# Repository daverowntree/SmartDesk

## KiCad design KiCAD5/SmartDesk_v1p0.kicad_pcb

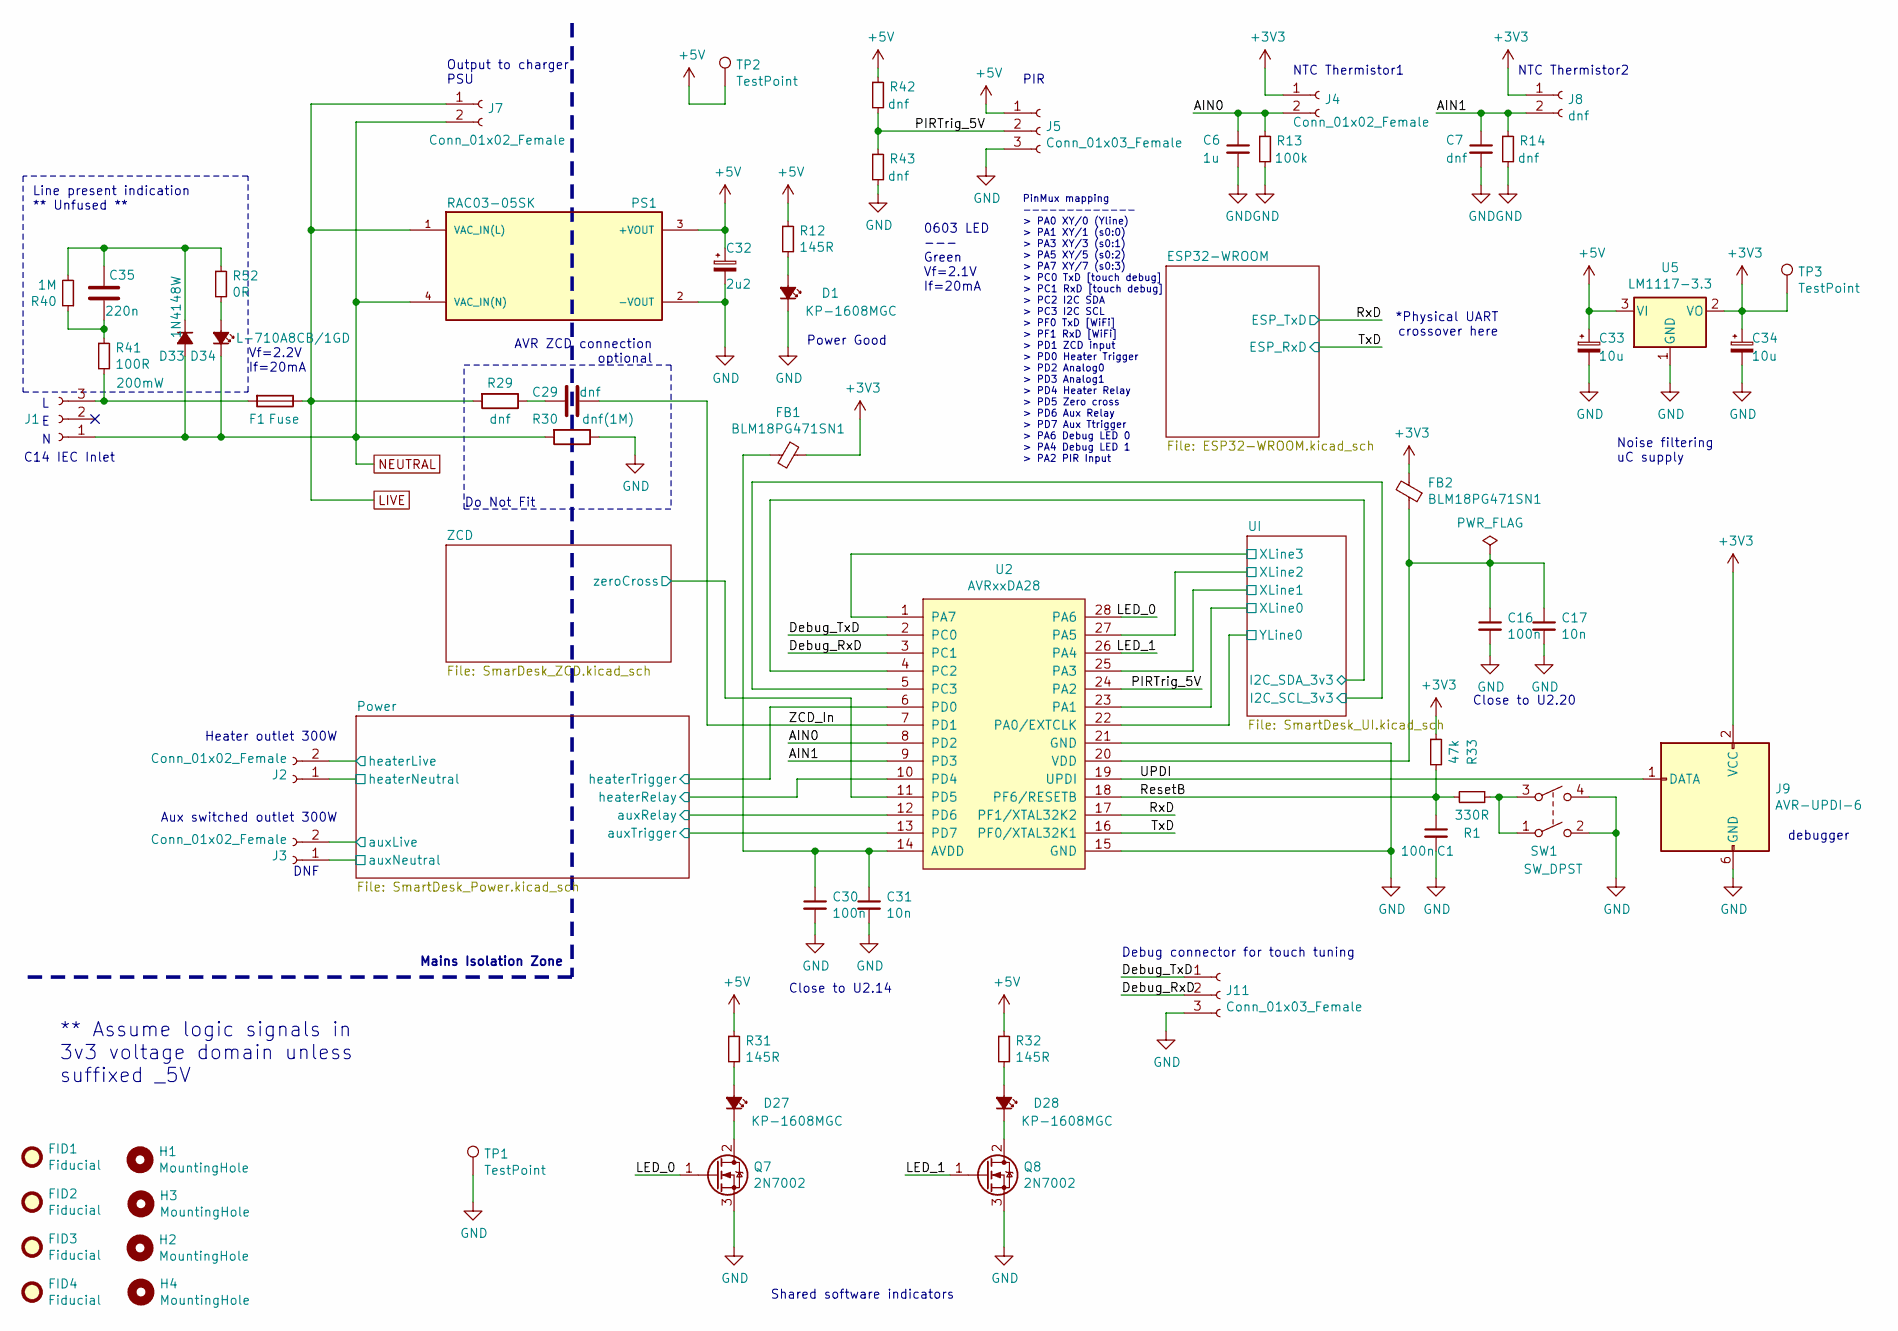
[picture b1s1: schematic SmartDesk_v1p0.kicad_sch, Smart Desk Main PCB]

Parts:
C1, C16, C30: 100n; C_0603_1608Metric
C6: 1u; C_0603_1608Metric
C7: dnf; C_0603_1608Metric
C17, C31: 10n; C_0603_1608Metric
C29: dnf; C_0805_2012Metric
C32: 2u2; C_0805_2012Metric
C33, C34: 10u; C_0805_2012Metric
C35: 220n; B32922C3224
D1, D27, D28: KP-1608MGC; LED_0603_1608Metric
D33: 1N4148W; D_SOD-323
D34: L-710A8CB/1GD; L-710A8CB
F1: Fuse; Bulgin-FX0321
FB1, FB2: BLM18PG471SN1; C_0603_1608Metric
FID1, FID2, FID3, FID4: Fiducial; Fiducial_Modern_CopperTop
H1, H2, H3, H4: MountingHole; MountingHole_4.3mm_M4
J1: Conn_01x03_Female; Bulgin-PX0580-PC
J2, J3, J7: Conn_01x02_Female; TerminalBlock_Phoenix_MKDS-3-2-5.08_1x02_P5.08mm_Horizontal
J4: Conn_01x02_Female; JST_PH_B2B-PH-K_1x02_P2.00mm_Vertical
J5: Conn_01x03_Female; JST_PH_B3B-PH-K_1x03_P2.00mm_Vertical
J8: dnf; JST_PH_B2B-PH-K_1x02_P2.00mm_Vertical
J9: AVR-UPDI-6; PinHeader_2x03_P2.54mm_Vertical
J11: Conn_01x03_Female; PinHeader_1x03_P2.54mm_Vertical
PS1: RAC03-05SK; CONV_RAC03-05SK
Q7, Q8: 2N7002; SOT-23
R1: 330R; R_0603_1608Metric
R12, R31, R32: 145R; R_0603_1608Metric
R13: 100k; R_0603_1608Metric
R14, R42, R43: dnf; R_0603_1608Metric
R29: dnf; R_0805_2012Metric
R30: dnf(1M); R_0805_2012Metric
R33: 47k; R_0603_1608Metric
R40: 1M; R_0603_1608Metric
R41: 100R; R_1206_3216Metric
R52: 0R; R_0603_1608Metric
SW1: SW_DPST; 2-1437565-8
TP1: TestPoint; TestPoint_Loop_D1.80mm_Drill1.0mm_Beaded
TP2, TP3: TestPoint; TestPoint_Pad_D2.0mm
U2: AVRxxDA28; SOIC-28W_7.5x17.9mm_P1.27mm
U5: LM1117-3.3; SOT-223-lm1117

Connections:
+3V3: C34.1, FB1.1, FB2.2, J4.1, J8.1, J9.2 (VCC), R33.1, TP3.1, U5.2 (VO); also elsewhere on the board
+5V: C32.1, C33.1, J5.1, PS1.3 (+VOUT), R12.1, R31.1, R32.1, R42.1, TP2.1, U5.3 (VI); also elsewhere on the board
/AIN0: C6.1, J4.2, R13.1, U2.8 (PD2)
/AIN1: C7.1, J8.2, R14.1, U2.9 (PD3)
/Debug_RxD: J11.2, U2.3 (PC1)
/Debug_TxD: J11.1, U2.2 (PC0)
/LED_0: Q7.1 (G), U2.28 (PA6)
/LED_1: Q8.1 (G), U2.26 (PA4)
/PIRTrig_5V: J5.2, R42.2, R43.1, U2.24 (PA2)
/Power/auxLive: J3.2; also elsewhere on the board
/Power/auxRelay: U2.12 (PD6); also elsewhere on the board
/Power/auxTrigger: U2.13 (PD7); also elsewhere on the board
/Power/heaterLive: J2.2; also elsewhere on the board
/Power/heaterRelay: U2.10 (PD4); also elsewhere on the board
/Power/heaterTrigger: U2.6 (PD0); also elsewhere on the board
/ResetB: C1.1, R1.2, R33.2, U2.18 (PF6/RESETB)
/RxD: U2.17 (PF1/XTAL32K2); also elsewhere on the board
/TxD: U2.16 (PF0/XTAL32K1); also elsewhere on the board
/UI/I2C_SCL_3v3: U2.5 (PC3); also elsewhere on the board
/UI/I2C_SDA_3v3: U2.4 (PC2); also elsewhere on the board
/UI/XLine0: U2.23 (PA1); also elsewhere on the board
/UI/XLine1: U2.25 (PA3); also elsewhere on the board
/UI/XLine2: U2.27 (PA5); also elsewhere on the board
/UI/XLine3: U2.1 (PA7); also elsewhere on the board
/UI/YLine0: U2.22 (PA0/EXTCLK); also elsewhere on the board
/UPDI: J9.1 (DATA), U2.19 (UPDI)
/ZCD/zeroCross: U2.11 (PD5); also elsewhere on the board
/ZCD_In: C29.1, U2.7 (PD1)
GND: C1.2, C6.2, C7.2, C16.2, C17.2, C30.2, C31.2, C32.2, C33.2, C34.2, D1.1 (K), J5.3, J9.6 (GND), J11.3, PS1.2 (-VOUT), Q7.3 (S), Q8.3 (S), R13.2, R14.2, R30.1, R43.2, SW1.2, SW1.4, TP1.1, U2.15 (GND), U2.21 (GND), U5.1 (GND); also elsewhere on the board
LIVE: F1.1, J7.1, PS1.1 (VAC_IN(L)), R29.2; also elsewhere on the board
NEUTRAL: D33.2 (A), D34.1 (K), J1.1, J2.1, J3.1, J7.2, PS1.4 (VAC_IN(N)), R30.2; also elsewhere on the board
unnamed: C16.1, C17.1, FB2.1, U2.20 (VDD)
unnamed: C29.2, R29.1
unnamed: C30.1, C31.1, FB1.2, U2.14 (AVDD)
unnamed: C35.1, R40.1, R41.1
unnamed: C35.2, D33.1 (K), R40.2, R52.1
unnamed: D1.2 (A), R12.2
unnamed: D27.1 (K), Q7.2 (D)
unnamed: D27.2 (A), R31.2
unnamed: D28.1 (K), Q8.2 (D)
unnamed: D28.2 (A), R32.2
unnamed: D34.2 (A), R52.2
unnamed: F1.2, J1.3, R41.2
unnamed: R1.1, SW1.1, SW1.3

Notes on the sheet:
DNF
Vf=2.2V If=20mA
Do Not Fit
Shared software indicators
C14 IEC Inlet
PIR
NTC Thermistor2
Close to U2.14
Mains Isolation Zone
Power Good
Heater outlet 300W
*Physical UART crossover here
Output to charger PSU
0603 LED --- Green Vf=2.1V If=20mA
Debug connector for touch tuning
Noise filtering uC supply
Line present indication ** Unfused **
PinMux mapping ------------- > PA0 XY/0 (Yline) > PA1 XY/1 (s0:0) > PA3 XY/3 (s0:1) > PA5 XY/5 (s0:2) > PA7 XY/7 (s0:3) > PC0 TxD [touch debug] > PC1 RxD [touch debug] > PC2 I2C SDA > PC3 I2C SCL > PF0 TxD [WiFi] > PF1 RxD [WiFi] > PD1 ZCD input > PD0 Heater Trigger > PD2 Analog0 > PD3 Analog1 > PD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
** Assume logic signals in 3v3 voltage domain unless suffixed _5V
Close to U2.20
debugger
Aux switched outlet 300W
NTC Thermistor1
AVR ZCD connection optional

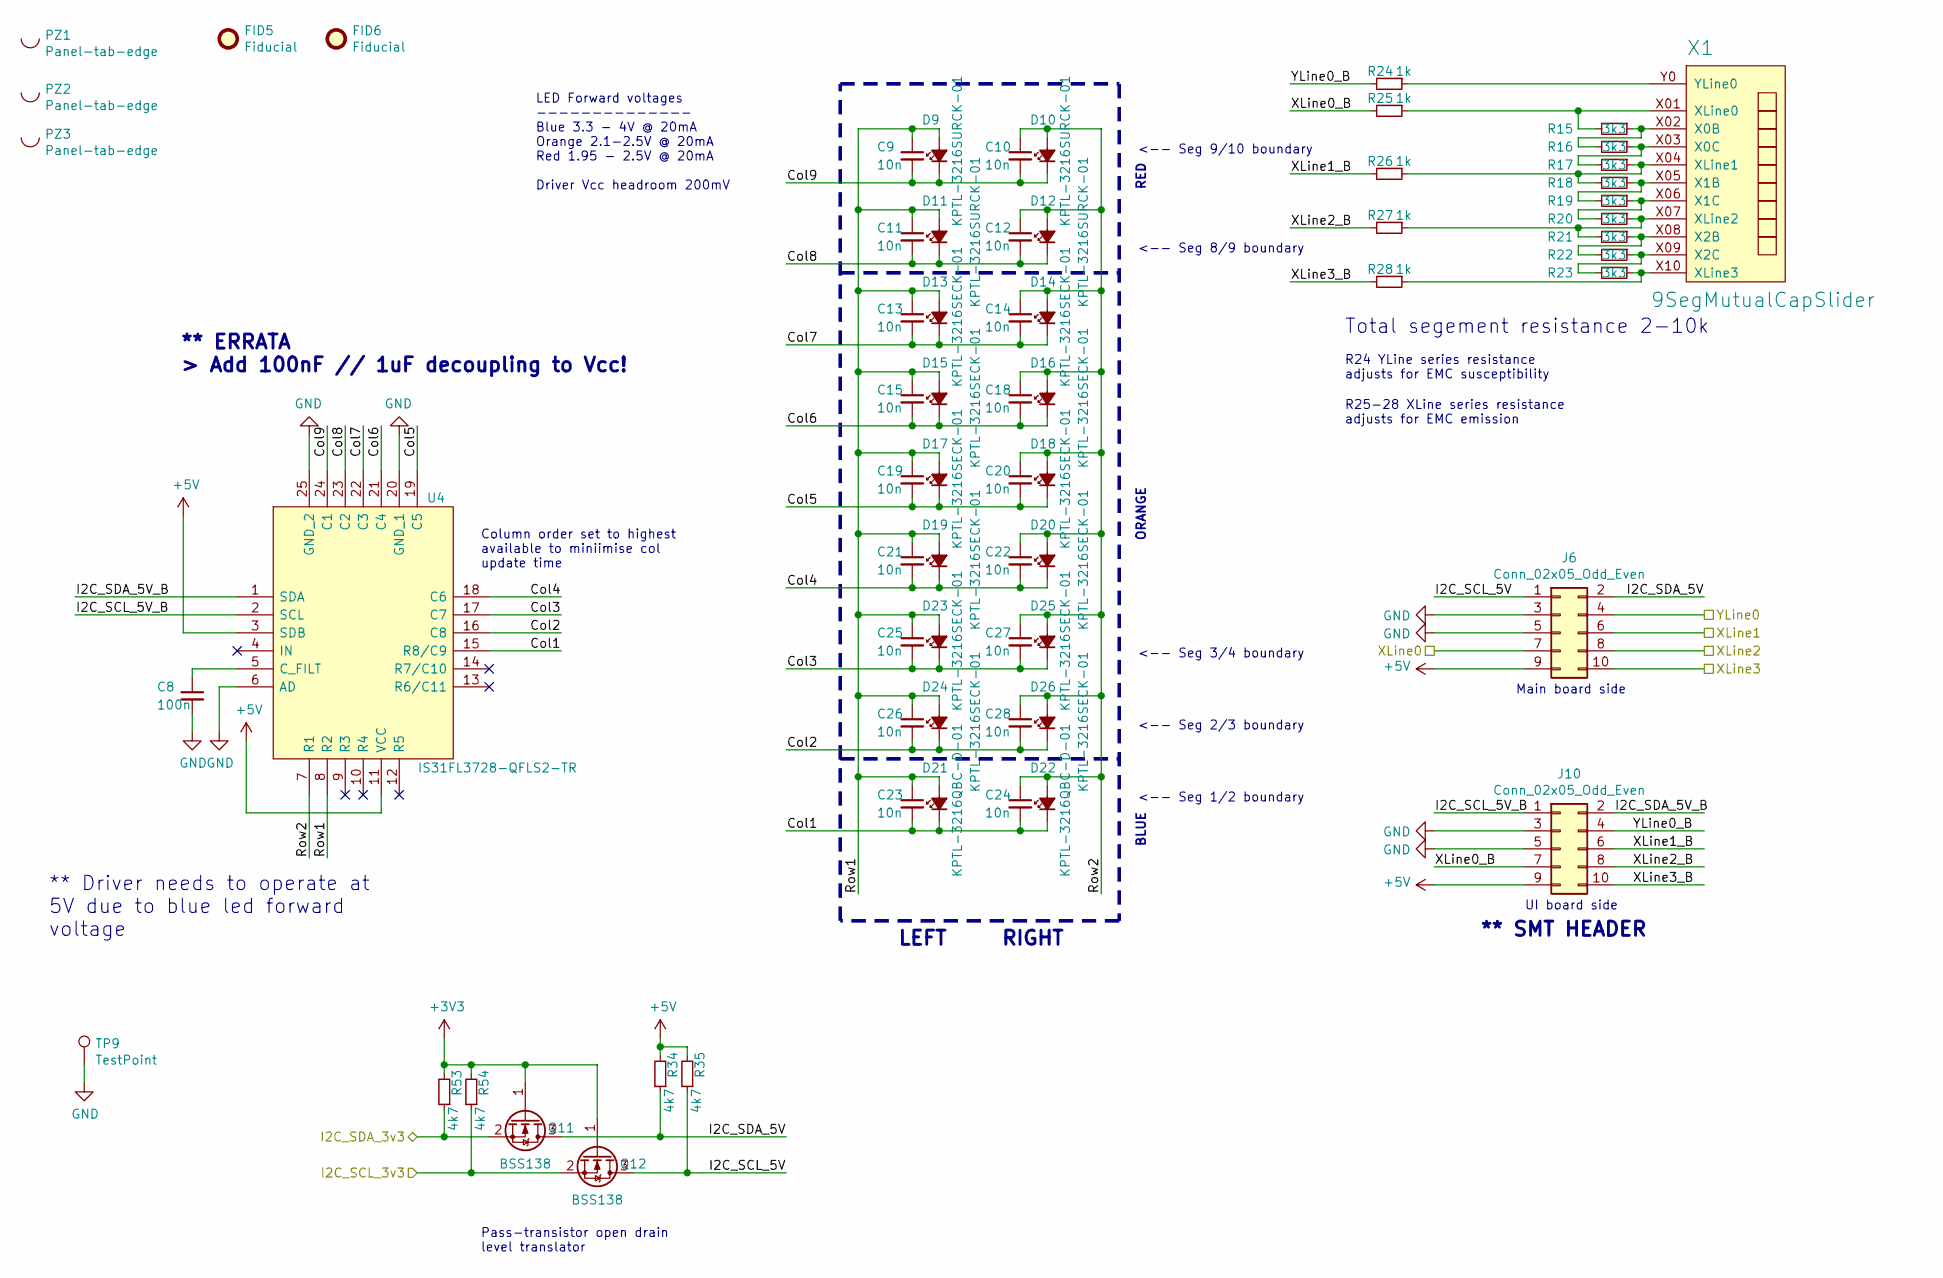
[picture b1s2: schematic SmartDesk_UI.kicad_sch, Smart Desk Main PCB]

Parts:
C8: 100n; C_0603_1608Metric
C9, C10, C11, C12, C13, C14, C15, C18, C19, C20, C21, C22, C23, C24, C25, C26, C27, C28: 10n; C_0603_1608Metric
D9, D10, D11, D12: KPTL-3216SURCK-01; VARC3216X102N
D13, D14, D15, D16, D17, D18, D19, D20, D23, D24, D25, D26: KPTL-3216SECK-01; VARC3216X102N
D21, D22: KPTL-3216QBC-D-01; VARC3216X102N
FID5, FID6: Fiducial; Fiducial_Modern_CopperTop
J6: Conn_02x05_Odd_Even; PinHeader_2x05_P2.54mm_Vertical
J10: Conn_02x05_Odd_Even; PinHeader_2x05_P2.54mm_Vertical_SMD
PZ1, PZ2, PZ3: Panel-tab-edge; mouse-bite-2mm-slot
Q11, Q12: BSS138; SOT-23
R15, R16, R17, R18, R19, R20, R21, R22, R23: 3k3; R_0603_1608Metric
R24, R25, R26, R27, R28: 1k; R_0603_1608Metric
R34, R35, R53, R54: 4k7; R_0603_1608Metric
TP9: TestPoint; TestPoint_Loop_D1.80mm_Drill1.0mm_Beaded
U4: IS31FL3728-QFLS2-TR; QFN50P400X400X80-25N-D; Manufacturer_Part_Number IS31FL3728-QFLS2-TR; Mouser Part Number 870-IS31FL3728QFLS2R
X1: 9SegMutualCapSlider

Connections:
+3V3: Q11.1 (G), Q12.1 (G), R53.2, R54.2; also elsewhere on the board
+5V: J6.9, J10.9, R34.2, R35.2, U4.3 (SDB), U4.11 (VCC); also elsewhere on the board
/UI/Col1: C23.2, C24.2, D21.1 (K), D22.1 (K), U4.15 (R8/C9)
/UI/Col2: C26.2, C28.2, D24.1 (K), D26.1 (K), U4.16 (C8)
/UI/Col3: C25.2, C27.2, D23.1 (K), D25.1 (K), U4.17 (C7)
/UI/Col4: C21.2, C22.2, D19.1 (K), D20.1 (K), U4.18 (C6)
/UI/Col5: C19.2, C20.2, D17.1 (K), D18.1 (K), U4.19 (C5)
/UI/Col6: C15.2, C18.2, D15.1 (K), D16.1 (K), U4.21 (C4)
/UI/Col7: C13.2, C14.2, D13.1 (K), D14.1 (K), U4.22 (C3)
/UI/Col8: C11.2, C12.2, D11.1 (K), D12.1 (K), U4.23 (C2)
/UI/Col9: C9.2, C10.2, D9.1 (K), D10.1 (K), U4.24 (C1)
/UI/I2C_SCL_3v3: Q12.2 (S), R54.1; also elsewhere on the board
/UI/I2C_SCL_5V: J6.1, Q12.3 (D), R35.1
/UI/I2C_SCL_5V_B: J10.1, U4.2 (SCL)
/UI/I2C_SDA_3v3: Q11.2 (S), R53.1; also elsewhere on the board
/UI/I2C_SDA_5V: J6.2, Q11.3 (D), R34.1
/UI/I2C_SDA_5V_B: J10.2, U4.1 (SDA)
/UI/Row1: C9.1, C11.1, C13.1, C15.1, C19.1, C21.1, C23.1, C25.1, C26.1, D9.2 (A), D11.2 (A), D13.2 (A), D15.2 (A), D17.2 (A), D19.2 (A), D21.2 (A), D23.2 (A), D24.2 (A), U4.8 (R2)
/UI/Row2: C10.1, C12.1, C14.1, C18.1, C20.1, C22.1, C24.1, C27.1, C28.1, D10.2 (A), D12.2 (A), D14.2 (A), D16.2 (A), D18.2 (A), D20.2 (A), D22.2 (A), D25.2 (A), D26.2 (A), U4.7 (R1)
/UI/XLine0: J6.7; also elsewhere on the board
/UI/XLine0_B: J10.7, R25.2
/UI/XLine1: J6.6; also elsewhere on the board
/UI/XLine1_B: J10.6, R26.2
/UI/XLine2: J6.8; also elsewhere on the board
/UI/XLine2_B: J10.8, R27.2
/UI/XLine3: J6.10; also elsewhere on the board
/UI/XLine3_B: J10.10, R28.2
/UI/YLine0: J6.4; also elsewhere on the board
/UI/YLine0_B: J10.4, R24.2
GND: C8.2, J6.3, J6.5, J10.3, J10.5, TP9.1, U4.6 (AD), U4.20 (GND_1), U4.25 (GND_2); also elsewhere on the board
unnamed: C8.1, U4.5 (C_FILT)
unnamed: R15.1, R16.2, X1.X02 (X0B)
unnamed: R15.2, R25.1, X1.X01 (XLine0)
unnamed: R16.1, R17.2, X1.X03 (X0C)
unnamed: R17.1, R18.2, R26.1, X1.X04 (XLine1)
unnamed: R18.1, R19.2, X1.X05 (X1B)
unnamed: R19.1, R20.2, X1.X06 (X1C)
unnamed: R20.1, R21.2, R27.1, X1.X07 (XLine2)
unnamed: R21.1, R22.2, X1.X08 (X2B)
unnamed: R22.1, R23.2, X1.X09 (X2C)
unnamed: R23.1, R28.1, X1.X10 (XLine3)
unnamed: R24.1, X1.Y0 (YLine0)

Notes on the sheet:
Main board side
LED Forward voltages -------------- Blue 3.3 - 4V @ 20mA Orange 2.1-2.5V @ 20mA Red 1.95 - 2.5V @ 20mA Driver Vcc headroom 200mV
RED
RIGHT
Column order set to highest available to miniimise col update time
<-- Seg 2/3 boundary
** Driver needs to operate at 5V due to blue led forward voltage
** SMT HEADER
Total segement resistance 2-10k
<-- Seg 3/4 boundary
<-- Seg 9/10 boundary
UI board side
** ERRATA > Add 100nF // 1uF decoupling to Vcc!
LEFT
<-- Seg 8/9 boundary
ORANGE
R25-28 XLine series resistance adjusts for EMC emission
R24 YLine series resistance adjusts for EMC susceptibility
<-- Seg 1/2 boundary
Pass-transistor open drain level translator
BLUE

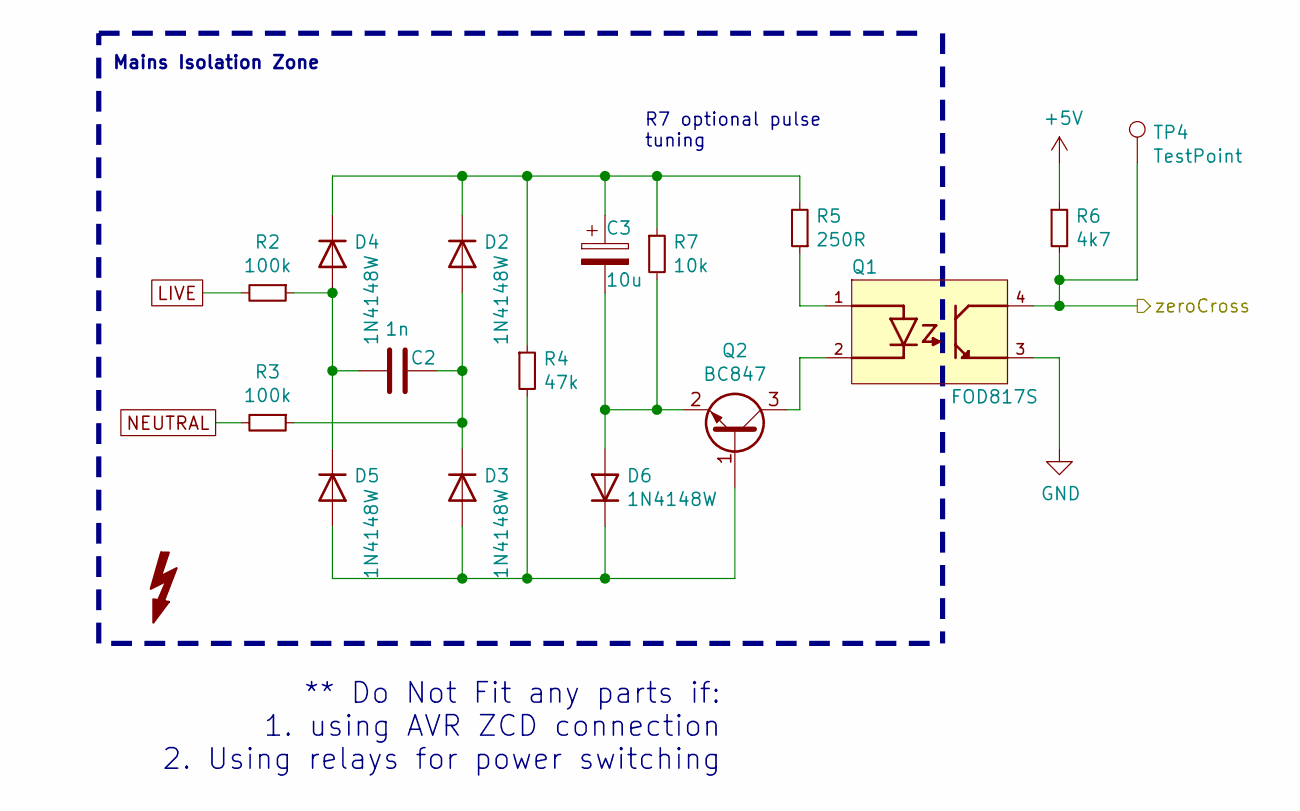
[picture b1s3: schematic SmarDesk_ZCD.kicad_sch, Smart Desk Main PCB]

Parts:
C2: 1n; C_0603_1608Metric
C3: 10u; C_0805_2012Metric
D2, D3, D4, D5, D6: 1N4148W; D_SOD-323
Q1: FOD817S; SOIC254P1016X385-4N
Q2: BC847; SOT-23
R2, R3: 100k; R_0603_1608Metric
R4: 47k; R_0603_1608Metric
R5: 250R; R_0603_1608Metric
R6: 4k7; R_0603_1608Metric
R7: 10k; R_0603_1608Metric
S1: SYM_Flash_Small; Symbol_Highvoltage_Type2_Silk_Small
TP4: TestPoint; TestPoint_Pad_D2.0mm

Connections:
+5V: R6.1; also elsewhere on the board
/ZCD/zeroCross: Q1.4, R6.2, TP4.1; also elsewhere on the board
GND: Q1.3; also elsewhere on the board
LIVE: R2.2; also elsewhere on the board
NEUTRAL: R3.2; also elsewhere on the board
unnamed: C2.1, D2.2 (A), D3.1 (K), R3.1
unnamed: C2.2, D4.2 (A), D5.1 (K), R2.1
unnamed: C3.1, D2.1 (K), D4.1 (K), R4.1, R5.2, R7.1
unnamed: C3.2, D6.2 (A), Q2.2 (E), R7.2
unnamed: D3.2 (A), D5.2 (A), D6.1 (K), Q2.1 (B), R4.2
unnamed: Q1.1, R5.1
unnamed: Q1.2, Q2.3 (C)

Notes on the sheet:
Mains Isolation Zone
R7 optional pulse tuning
** Do Not Fit any parts if: 1. using AVR ZCD connection 2. Using relays for power switching

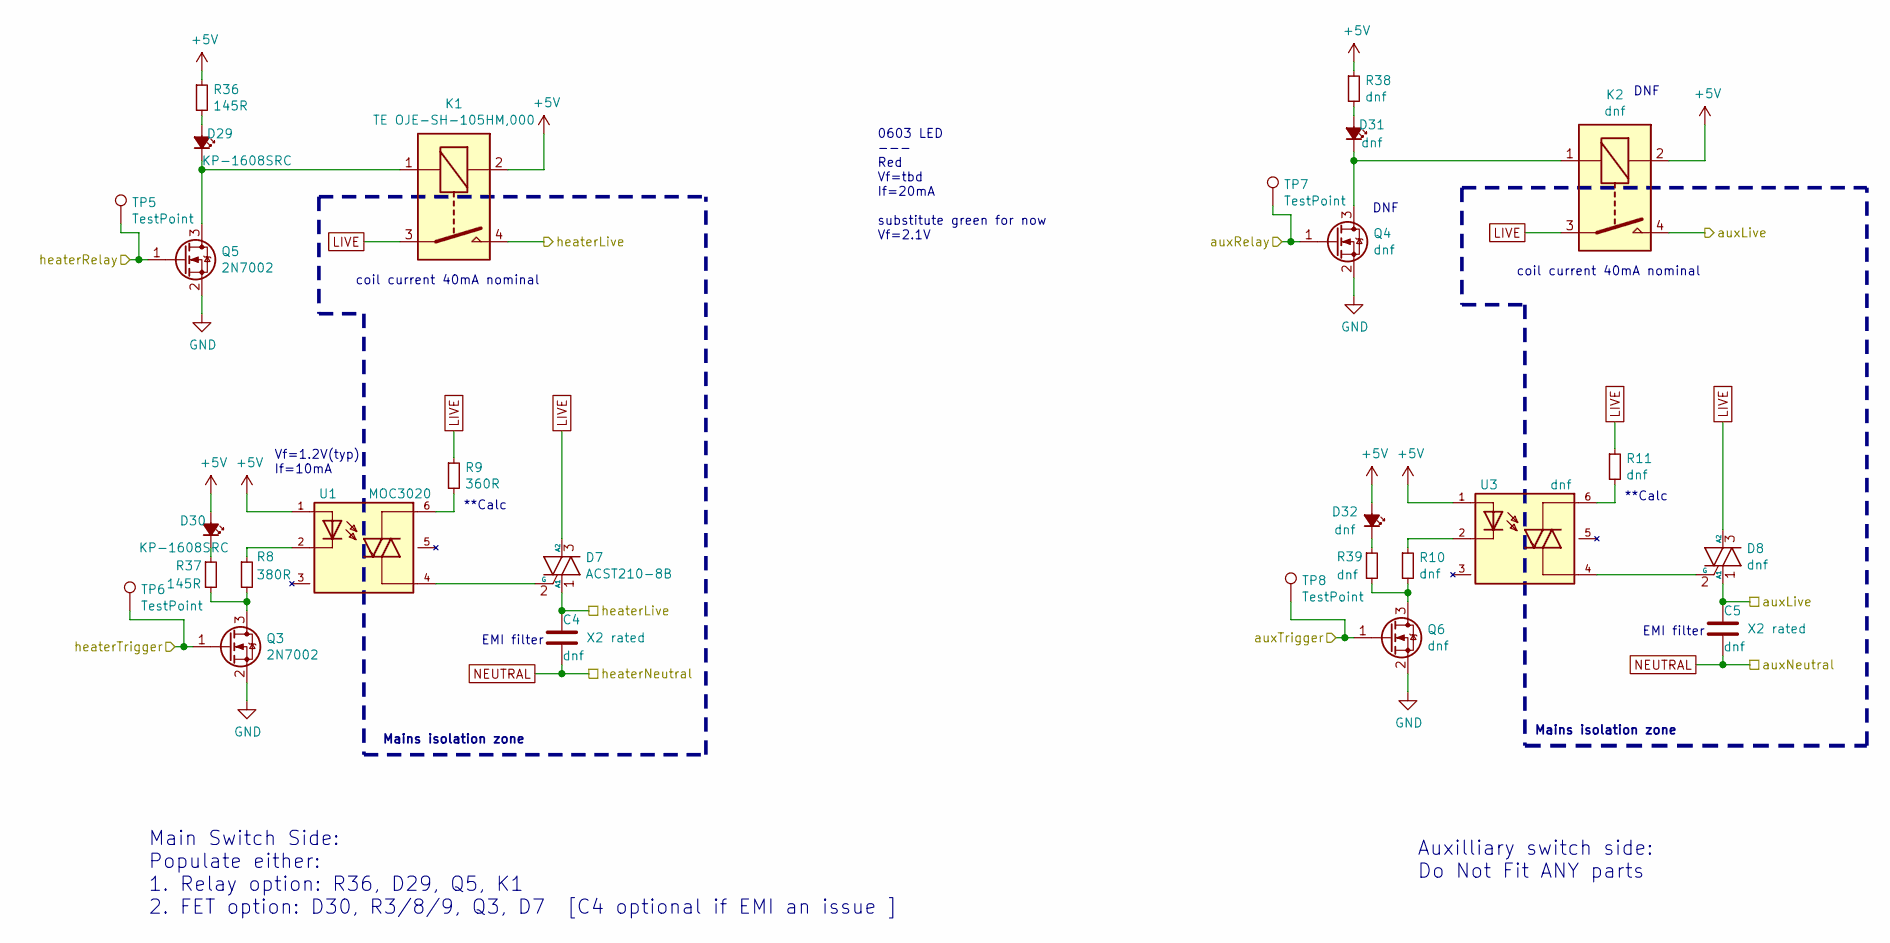
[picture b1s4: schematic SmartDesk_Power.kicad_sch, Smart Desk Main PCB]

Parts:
C4, C5: dnf; B32921C3223M289; Rating X2 rated
D7: ACST210-8B; DPAK228P987X240-3N
D8: dnf; DPAK228P987X240-3N
D29, D30: KP-1608SRC; LED_0603_1608Metric
D31, D32: dnf; LED_0603_1608Metric
K1: TE OJE-SH-105HM,000; TE_OJE-SH-105HM
K2: dnf; TE_OJE-SH-105HM
Q3, Q5: 2N7002; SOT-23
Q4, Q6: dnf; SOT-23
R8: 380R; R_0603_1608Metric
R9: 360R; R_0603_1608Metric
R10, R11, R38, R39: dnf; R_0603_1608Metric
R36, R37: 145R; R_0603_1608Metric
TP5, TP6, TP7, TP8: TestPoint; TestPoint_Pad_D2.0mm
U1: MOC3020; MOC302X-SON6
U3: dnf; MOC302X-SON6

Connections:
+5V: D30.2 (A), D32.2 (A), K1.2, K2.2, R36.1, R38.1, U1.1, U3.1; also elsewhere on the board
/Power/auxLive: C5.1, D8.1 (A1), K2.4; also elsewhere on the board
/Power/auxRelay: Q4.1 (G), TP7.1; also elsewhere on the board
/Power/auxTrigger: Q6.1 (G), TP8.1; also elsewhere on the board
/Power/heaterLive: C4.1, D7.1 (A1), K1.4; also elsewhere on the board
/Power/heaterRelay: Q5.1 (G), TP5.1; also elsewhere on the board
/Power/heaterTrigger: Q3.1 (G), TP6.1; also elsewhere on the board
GND: Q3.2 (S), Q4.2 (S), Q5.2 (S), Q6.2 (S); also elsewhere on the board
LIVE: D7.3 (A2), D8.3 (A2), K1.3, K2.3, R9.1, R11.1; also elsewhere on the board
NEUTRAL: C4.2, C5.2; also elsewhere on the board
unnamed: D7.2 (G), U1.4
unnamed: D8.2 (G), U3.4
unnamed: D29.1 (K), K1.1, Q5.3 (D)
unnamed: D29.2 (A), R36.2
unnamed: D30.1 (K), R37.1
unnamed: D31.1 (K), K2.1, Q4.3 (D)
unnamed: D31.2 (A), R38.2
unnamed: D32.1 (K), R39.1
unnamed: Q3.3 (D), R8.2, R37.2
unnamed: Q6.3 (D), R10.2, R39.2
unnamed: R8.1, U1.2
unnamed: R9.2, U1.6
unnamed: R10.1, U3.2
unnamed: R11.2, U3.6

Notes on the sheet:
Mains isolation zone
Auxilliary switch side: Do Not Fit ANY parts
0603 LED --- Red Vf=tbd If=20mA substitute green for now Vf=2.1V
DNF
EMI filter
**Calc
Main Switch Side: Populate either: 1. Relay option: R36, D29, Q5, K1 2. FET option: D30, R3/8/9, Q3, D7 [C4 optional if EMI an issue ]
coil current 40mA nominal
Vf=1.2V(typ) If=10mA

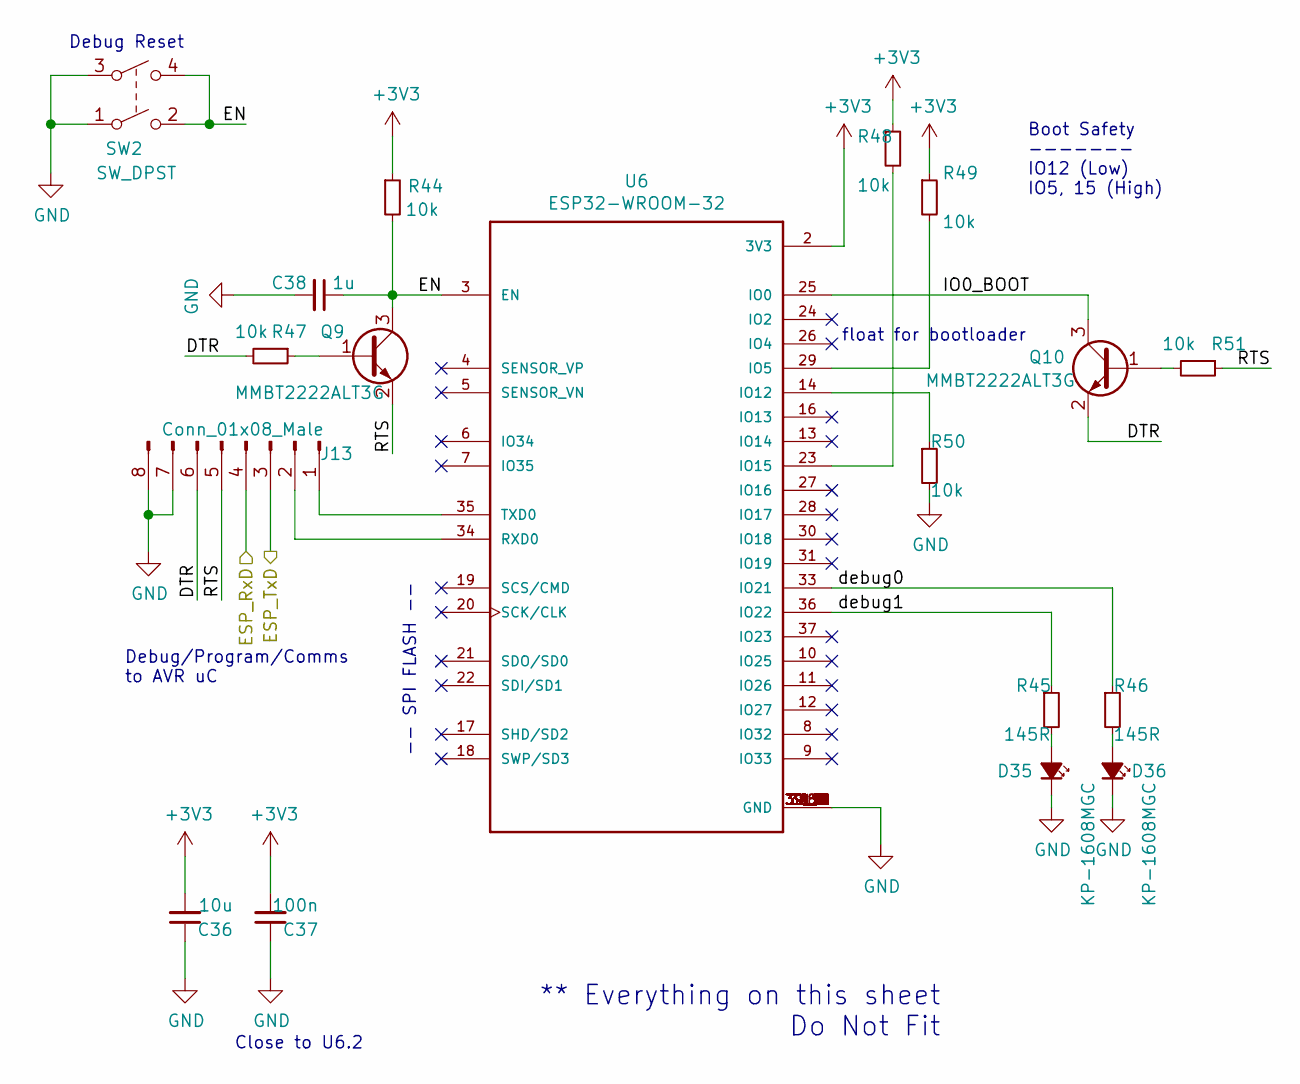
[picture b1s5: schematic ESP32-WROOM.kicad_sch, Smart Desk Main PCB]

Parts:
C36: 10u; C_0603_1608Metric
C37: 100n; C_0603_1608Metric
C38: 1u; C_0603_1608Metric
D35, D36: KP-1608MGC; LED_0603_1608Metric
J13: Conn_01x08_Male; Pin_Header_Straight_2x04_Pitch2.54mm
Q9, Q10: MMBT2222ALT3G; SOT-23
R44, R47, R48, R49, R50, R51: 10k; R_0603_1608Metric
R45, R46: 145R; R_0603_1608Metric
SW2: SW_DPST; 2-1437565-8
U6: ESP32-WROOM-32; MODULE_ESP32-WROOM-32

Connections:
+3V3: C36.2, C37.2, R44.1, R48.1, R49.1, U6.2 (3V3); also elsewhere on the board
/ESP32-WROOM/DTR: J13.6, Q10.2 (E), R47.2
/ESP32-WROOM/EN: C38.1, Q9.3 (C), R44.2, SW2.2, SW2.4, U6.3 (EN)
/ESP32-WROOM/IO0_BOOT: Q10.3 (C), U6.25 (IO0)
/ESP32-WROOM/RTS: J13.5, Q9.2 (E), R51.1
/ESP32-WROOM/debug0: R46.1, U6.33 (IO21)
/ESP32-WROOM/debug1: R45.1, U6.36 (IO22)
/RxD: J13.3; also elsewhere on the board
/TxD: J13.4; also elsewhere on the board
GND: C36.1, C37.1, C38.2, D35.1 (K), D36.1 (K), J13.7, J13.8, R50.2, SW2.1, SW2.3, U6.1 (GND), U6.15 (GND), U6.38 (GND), U6.39_1 (GND), U6.39_2 (GND), U6.39_3 (GND), U6.39_4 (GND), U6.39_5 (GND), U6.39_6 (GND), U6.39_7 (GND), U6.39_8 (GND), U6.39_9 (GND), U6.39_10 (GND), U6.39_11 (GND), U6.39_12 (GND), U6.39_13 (GND), U6.39_14 (GND), U6.39_15 (GND), U6.39_16 (GND), U6.39_17 (GND), U6.39_18 (GND), U6.39_19 (GND), U6.39_20 (GND), U6.39_21 (GND); also elsewhere on the board
unnamed: D35.2 (A), R45.2
unnamed: D36.2 (A), R46.2
unnamed: J13.1, U6.35 (TXD0)
unnamed: J13.2, U6.34 (RXD0)
unnamed: Q9.1 (B), R47.1
unnamed: Q10.1 (B), R51.2
unnamed: R48.2, U6.23 (IO15)
unnamed: R49.2, U6.29 (IO5)
unnamed: R50.1, U6.14 (IO12)

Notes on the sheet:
Boot Safety ------- IO12 (Low) IO5, 15 (High)
** Everything on this sheet Do Not Fit
Debug/Program/Comms to AVR uC
Debug Reset
float for bootloader
Close to U6.2
-- SPI FLASH --

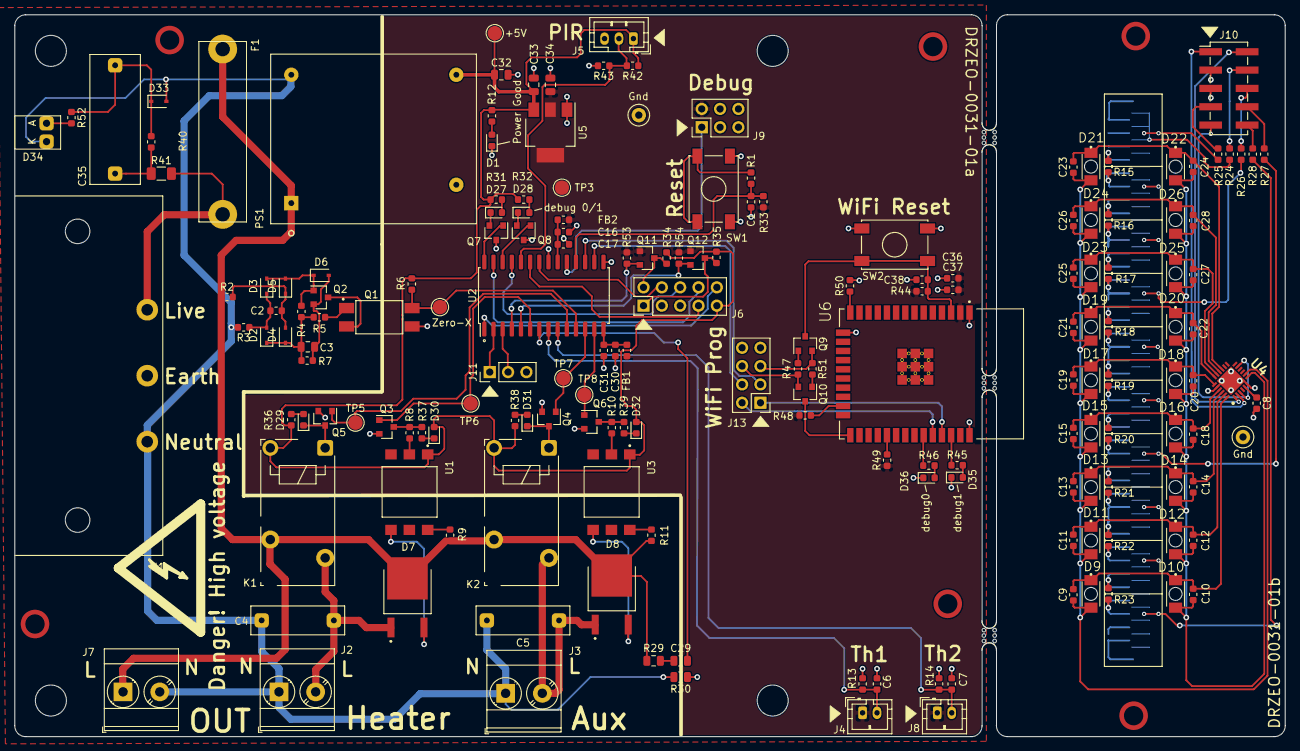
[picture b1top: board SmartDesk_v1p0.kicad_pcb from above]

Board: 2 copper layers, 176.0 x 100.0 mm, 190 parts (1 on the bottom side), 112 nets.

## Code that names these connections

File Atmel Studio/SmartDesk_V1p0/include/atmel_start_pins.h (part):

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/**
 * \brief Set YLine0 input/sense configuration
 *
 * Enable/disable YLine0 digital input buffer and pin change interrupt,
 * select pin interrupt edge/level sensing mode
 *
 * \param[in] isc PORT_ISC_INTDISABLE_gc    = Iterrupt disabled but input buffer enabled
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/**
 * \brief Set XLine0 input/sense configuration
 *
 * Enable/disable XLine0 digital input buffer and pin change interrupt,
 * select pin interrupt edge/level sensing mode
 *
 * \param[in] isc PORT_ISC_INTDISABLE_gc    = Iterrupt disabled but input buffer enabled
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/**
 * \brief Set XLine1 input/sense configuration
 *
 * Enable/disable XLine1 digital input buffer and pin change interrupt,
 * select pin interrupt edge/level sensing mode
 *
 * \param[in] isc PORT_ISC_INTDISABLE_gc    = Iterrupt disabled but input buffer enabled
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/**
 * \brief Set XLine2 input/sense configuration
 *
 * Enable/disable XLine2 digital input buffer and pin change interrupt,
 * select pin interrupt edge/level sensing mode
 *
 * \param[in] isc PORT_ISC_INTDISABLE_gc    = Iterrupt disabled but input buffer enabled
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/**
 * \brief Set XLine3 input/sense configuration
 *
 * Enable/disable XLine3 digital input buffer and pin change interrupt,
 * select pin interrupt edge/level sensing mode
 *
 * \param[in] isc PORT_ISC_INTDISABLE_gc    = Iterrupt disabled but input buffer enabled
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/**
 * \brief Set debug_TxD input/sense configuration
 *
 * Enable/disable debug_TxD digital input buffer and pin change interrupt,
 * select pin interrupt edge/level sensing mode
 *
 * \param[in] isc PORT_ISC_INTDISABLE_gc    = Iterrupt disabled but input buffer enabled
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/**
 * \brief Set debug_RxD input/sense configuration
 *
 * Enable/disable debug_RxD digital input buffer and pin change interrupt,
 * select pin interrupt edge/level sensing mode
 *
 * \param[in] isc PORT_ISC_INTDISABLE_gc    = Iterrupt disabled but input buffer enabled
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/**
 * \brief Set heaterTrigger input/sense configuration
 *
 * Enable/disable heaterTrigger digital input buffer and pin change interrupt,
 * select pin interrupt edge/level sensing mode
 *
 * \param[in] isc PORT_ISC_INTDISABLE_gc    = Iterrupt disabled but input buffer enabled
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/**
 * \brief Set AIN0 input/sense configuration
 *
 * Enable/disable AIN0 digital input buffer and pin change interrupt,
 * select pin interrupt edge/level sensing mode
 *
 * \param[in] isc PORT_ISC_INTDISABLE_gc    = Iterrupt disabled but input buffer enabled
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/**
 * \brief Set AIN1 input/sense configuration
 *
 * Enable/disable AIN1 digital input buffer and pin change interrupt,
 * select pin interrupt edge/level sensing mode
 *
 * \param[in] isc PORT_ISC_INTDISABLE_gc    = Iterrupt disabled but input buffer enabled
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/**
 * \brief Set heaterRelay input/sense configuration
 *
 * Enable/disable heaterRelay digital input buffer and pin change interrupt,
 * select pin interrupt edge/level sensing mode
 *
 * \param[in] isc PORT_ISC_INTDISABLE_gc    = Iterrupt disabled but input buffer enabled
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/**
 * \brief Set zeroCross input/sense configuration
 *
 * Enable/disable zeroCross digital input buffer and pin change interrupt,
 * select pin interrupt edge/level sensing mode
 *
 * \param[in] isc PORT_ISC_INTDISABLE_gc    = Iterrupt disabled but input buffer enabled
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/**
 * \brief Set auxRelay input/sense configuration
 *
 * Enable/disable auxRelay digital input buffer and pin change interrupt,
 * select pin interrupt edge/level sensing mode
 *
 * \param[in] isc PORT_ISC_INTDISABLE_gc    = Iterrupt disabled but input buffer enabled
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/**
 * \brief Set auxTrigger input/sense configuration
 *
 * Enable/disable auxTrigger digital input buffer and pin change interrupt,
 * select pin interrupt edge/level sensing mode
 *
 * \param[in] isc PORT_ISC_INTDISABLE_gc    = Iterrupt disabled but input buffer enabled
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
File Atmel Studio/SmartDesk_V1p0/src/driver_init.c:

/**
 * \file
 *
 * \brief Driver initialization.
 *
 (c) 2020 Microchip Technology Inc. and its subsidiaries.

    Subject to your compliance with these terms,you may use this software and
    any derivatives exclusively with Microchip products.It is your responsibility
    to comply with third party license terms applicable to your use of third party
    software (including open source software) that may accompany Microchip software.

    THIS SOFTWARE IS SUPPLIED BY MICROCHIP "AS IS". NO WARRANTIES, WHETHER
    EXPRESS, IMPLIED OR STATUTORY, APPLY TO THIS SOFTWARE, INCLUDING ANY IMPLIED
    WARRANTIES OF NON-INFRINGEMENT, MERCHANTABILITY, AND FITNESS FOR A
    PARTICULAR PURPOSE.

    IN NO EVENT WILL MICROCHIP BE LIABLE FOR ANY INDIRECT, SPECIAL, PUNITIVE,
    INCIDENTAL OR CONSEQUENTIAL LOSS, DAMAGE, COST OR EXPENSE OF ANY KIND
    WHATSOEVER RELATED TO THE SOFTWARE, HOWEVER CAUSED, EVEN IF MICROCHIP HAS
    BEEN ADVISED OF THE POSSIBILITY OR THE DAMAGES ARE FORESEEABLE. TO THE
    FULLEST EXTENT ALLOWED BY LAW, MICROCHIP'S TOTAL LIABILITY ON ALL CLAIMS IN
    ANY WAY RELATED TO THIS SOFTWARE WILL NOT EXCEED THE AMOUNT OF FEES, IF ANY,
    THAT YOU HAVE PAID DIRECTLY TO MICROCHIP FOR THIS SOFTWARE.
 *
 */

/*
 * Code generated by START.
 *
 * This file will be overwritten when reconfiguring your START project.
 * Please copy examples or other code you want to keep to a separate file
 * to avoid losing it when reconfiguring.
 */

#include "driver_init.h"
#include <system.h>

/* configure the pins and initialize the registers */
void USART_initialization(void)
{

	// Set pin direction to input
	debug_RxD_set_dir(PORT_DIR_IN);

	debug_RxD_set_pull_mode(
	    // <y> Pull configuration
	    // <id> pad_pull_config
	    // <PORT_PULL_OFF"> Off
	    // <PORT_PULL_UP"> Pull-up
	    PORT_PULL_OFF);

	// Set pin direction to output

	debug_TxD_set_level(
	    // <y> Initial level
	    // <id> pad_initial_level
	    // <false"> Low
	    // <true"> High
	    false);

	debug_TxD_set_dir(PORT_DIR_OUT);

	USART_init();
}

/* configure the pins and initialize the registers */
void USART_0_initialization(void)
{

	// Set pin direction to input
	RxD_set_dir(PORT_DIR_IN);

	RxD_set_pull_mode(
	    // <y> Pull configuration
	    // <id> pad_pull_config
	    // <PORT_PULL_OFF"> Off
	    // <PORT_PULL_UP"> Pull-up
	    PORT_PULL_OFF);

	// Set pin direction to output

	TxD_set_level(
	    // <y> Initial level
	    // <id> pad_initial_level
	    // <false"> Low
	    // <true"> High
	    false);

	TxD_set_dir(PORT_DIR_OUT);

	USART_0_init();
}

/* configure pins and initialize registers */
void ZCD_0_initialization(void)
{

	// Disable digital input buffer
	ZCD_set_isc(PORT_ISC_INPUT_DISABLE_gc);
	// Disable pull-up resistor
	ZCD_set_pull_mode(PORT_PULL_OFF);

	ZCD_0_init();
}

/* configure pins and initialize registers */
void I2C_0_initialization(void)
{

	SCL_set_level(
	    // <y> Initial level
	    // <id> pad_initial_level
	    // <false"> Low
	    // <true"> High
	    false); // 

	SCL_set_dir(
	    // <y> Pin direction
	    // <id> pad_dir
	    // <PORT_DIR_OFF"> Off
	    // <PORT_DIR_IN"> In
	    // <PORT_DIR_OUT"> Out
	    PORT_DIR_OUT);

	SCL_set_pull_mode(
	    // <y> Pull configuration
	    // <id> pad_pull_config
	    // <PORT_PULL_OFF"> Off
	    // <PORT_PULL_UP"> Pull-up
	    PORT_PULL_OFF);

	SCL_set_inverted(
	    // <y> Invert I/O on pin
	    // <id> pad_invert
	    // <false"> Not inverted
	    // <true"> Inverted
	    false);

	SCL_set_isc(
	    // <y> Pin Input/Sense Configuration
	    // <id> pad_isc
	    // <PORT_ISC_INTDISABLE_gc"> Interrupt disabled but input buffer enabled
	    // <PORT_ISC_BOTHEDGES_gc"> Sense Both Edges
	    // <PORT_ISC_RISING_gc"> Sense Rising Edge
	    // <PORT_ISC_FALLING_gc"> Sense Falling Edge
	    // <PORT_ISC_INPUT_DISABLE_gc"> Digital Input Buffer disabled
	    // <PORT_ISC_LEVEL_gc"> Sense low Level
	    PORT_ISC_INTDISABLE_gc);

	/* set the alternate pin mux */

	PORTMUX.TWIROUTEA |= PORTMUX_TWI01_bm;

	SDA_set_level(
	    // <y> Initial level
	    // <id> pad_initial_level
	    // <false"> Low
	    // <true"> High
	    false); // 

	SDA_set_dir(
	    // <y> Pin direction
	    // <id> pad_dir
	    // <PORT_DIR_OFF"> Off
	    // <PORT_DIR_IN"> In
	    // <PORT_DIR_OUT"> Out
	    PORT_DIR_OUT);

	SDA_set_pull_mode(
	    // <y> Pull configuration
	    // <id> pad_pull_config
	    // <PORT_PULL_OFF"> Off
	    // <PORT_PULL_UP"> Pull-up
	    PORT_PULL_OFF);

	SDA_set_inverted(
	    // <y> Invert I/O on pin
	    // <id> pad_invert
	    // <false"> Not inverted
	    // <true"> Inverted
	    false);

	SDA_set_isc(
	    // <y> Pin Input/Sense Configuration
	    // <id> pad_isc
	    // <PORT_ISC_INTDISABLE_gc"> Interrupt disabled but input buffer enabled
	    // <PORT_ISC_BOTHEDGES_gc"> Sense Both Edges
	    // <PORT_ISC_RISING_gc"> Sense Rising Edge
	    // <PORT_ISC_FALLING_gc"> Sense Falling Edge
	    // <PORT_ISC_INPUT_DISABLE_gc"> Digital Input Buffer disabled
	    // <PORT_ISC_LEVEL_gc"> Sense low Level
	    PORT_ISC_INTDISABLE_gc);

	/* set the alternate pin mux */

	PORTMUX.TWIROUTEA |= PORTMUX_TWI01_bm;

	I2C_0_init();
}

/* Configure pins and initialize registers */
void ADC_0_initialization(void)
{

	ADC_0_init();
}

/**
 * \brief System initialization
 */
void system_init()
{
	mcu_init();

	/* PORT setting on PA2 */

	// Set pin direction to input
	PIR_set_dir(PORT_DIR_IN);

	PIR_set_pull_mode(
	    // <y> Pull configuration
	    // <id> pad_pull_config
	    // <PORT_PULL_OFF"> Off
	    // <PORT_PULL_UP"> Pull-up
	    PORT_PULL_OFF);

	/* PORT setting on PA4 */

	// Set pin direction to output

	LED1_set_level(
	    // <y> Initial level
	    // <id> pad_initial_level
	    // <false"> Low
	    // <true"> High
	    false);

	LED1_set_dir(PORT_DIR_OUT);

	/* PORT setting on PA6 */

	// Set pin direction to output

	LED0_set_level(
	    // <y> Initial level
	    // <id> pad_initial_level
	    // <false"> Low
	    // <true"> High
	    false);

	LED0_set_dir(PORT_DIR_OUT);

	/* PORT setting on PD0 */

	// Set pin direction to output

	heaterTrigger_set_level(
	    // <y> Initial level
	    // <id> pad_initial_level
	    // <false"> Low
	    // <true"> High
	    false);

	heaterTrigger_set_dir(PORT_DIR_OUT);

	/* PORT setting on PD2 */

	// Disable digital input buffer
	AIN0_set_isc(PORT_ISC_INPUT_DISABLE_gc);
	// Disable pull-up resistor
	AIN0_set_pull_mode(PORT_PULL_OFF);

	/* PORT setting on PD3 */

	// Disable digital input buffer
	AIN1_set_isc(PORT_ISC_INPUT_DISABLE_gc);
	// Disable pull-up resistor
	AIN1_set_pull_mode(PORT_PULL_OFF);

	/* PORT setting on PD4 */

	// Set pin direction to output

	heaterRelay_set_level(
	    // <y> Initial level
	    // <id> pad_initial_level
	    // <false"> Low
	    // <true"> High
	    false);

	heaterRelay_set_dir(PORT_DIR_OUT);

	/* PORT setting on PD5 */

	// Set pin direction to input
	zeroCross_set_dir(PORT_DIR_IN);

	zeroCross_set_pull_mode(
	    // <y> Pull configuration
	    // <id> pad_pull_config
	    // <PORT_PULL_OFF"> Off
	    // <PORT_PULL_UP"> Pull-up
	    PORT_PULL_OFF);

	/* PORT setting on PD6 */

	// Set pin direction to output

	auxRelay_set_level(
	    // <y> Initial level
	    // <id> pad_initial_level
	    // <false"> Low
	    // <true"> High
	    false);

	auxRelay_set_dir(PORT_DIR_OUT);

	/* PORT setting on PD7 */

	// Set pin direction to output

	auxTrigger_set_level(
	    // <y> Initial level
	    // <id> pad_initial_level
	    // <false"> Low
	    // <true"> High
	    false);

	auxTrigger_set_dir(PORT_DIR_OUT);

	CLKCTRL_init();

	USART_initialization();

	USART_0_initialization();

	SLPCTRL_init();

	CPUINT_init();

	ZCD_0_initialization();

	I2C_0_initialization();

	ADC_0_initialization();

	Timer_init();

	BOD_init();
}
